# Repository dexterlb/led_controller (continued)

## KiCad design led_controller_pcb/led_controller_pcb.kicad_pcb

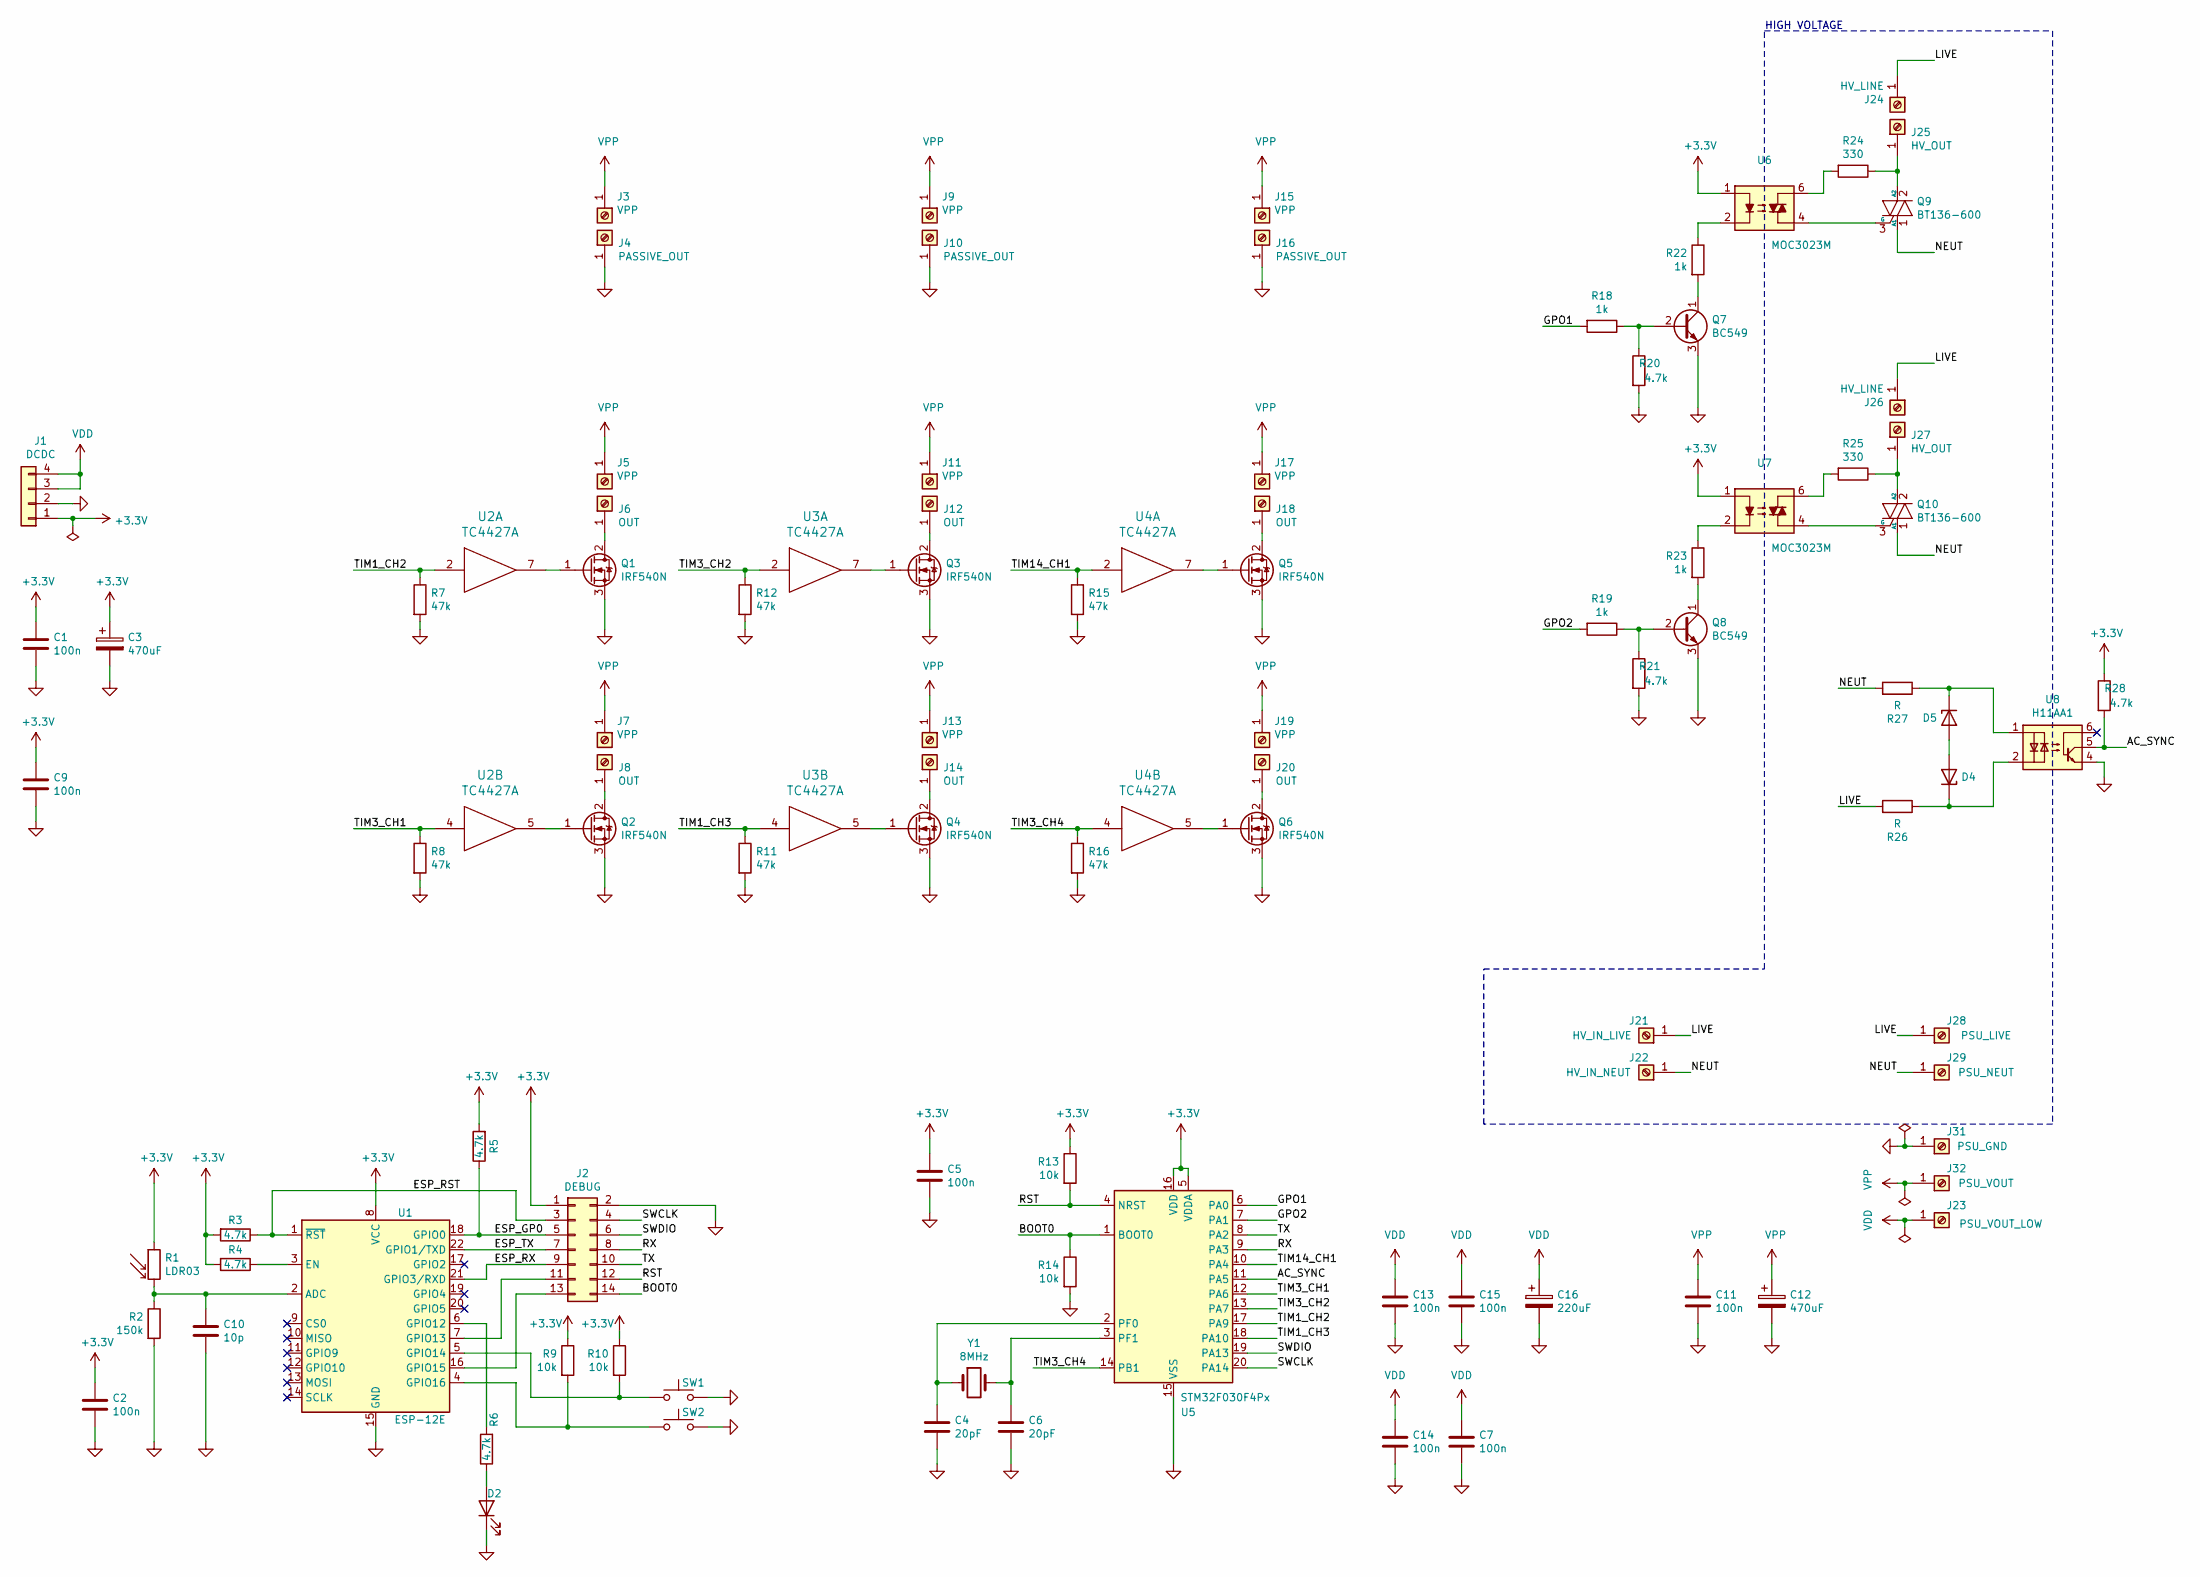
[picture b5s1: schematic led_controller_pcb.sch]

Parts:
C1, C2, C5, C7, C9, C11, C13, C14, C15: 100n; C_0805_2012Metric_Pad1.15x1.40mm_HandSolder
C3: 470uF; CP_Elec_6.3x7.7
C4, C6: 20pF; C_0805_2012Metric_Pad1.15x1.40mm_HandSolder
C10: 10p; C_0805_2012Metric_Pad1.15x1.40mm_HandSolder
C12: 470uF; CP_Radial_D8.0mm_P3.50mm
C16: 220uF; CP_Elec_6.3x7.7
D2: LED; LED_D5.0mm
D4, D5: 1N47xxA; D_DO-41_SOD81_P10.16mm_Horizontal
J1: DCDC; PinHeader_1x04_P2.54mm_Vertical
J2: DEBUG; PinHeader_2x07_P2.54mm_Vertical
J3, J5, J7, J9, J11, J13, J15, J17, J19: VPP; 1PIN_DG306
J4, J10, J16: PASSIVE_OUT; 1PIN_DG306
J6, J8, J12, J14, J18, J20: OUT; 1PIN_DG306
J21: HV_IN_LIVE; 1PIN_DG306
J22: HV_IN_NEUT; 1PIN_DG306
J23: PSU_VOUT_LOW; 1PIN_DG306
J24, J26: HV_LINE; 1PIN_DG306
J25, J27: HV_OUT; 1PIN_DG306
J28: PSU_LIVE; 1PIN_DG306
J29: PSU_NEUT; 1PIN_DG306
J31: PSU_GND; 1PIN_DG306
J32: PSU_VOUT; 1PIN_DG306
Q1, Q2, Q3, Q4, Q5, Q6: IRF540N; TO-220-3_Vertical
Q7, Q8: BC549; TO-92
Q9, Q10: BT136-600; TO-220-3_Vertical
R1: LDR03; PinHeader_1x02_P2.54mm_Vertical
R2: 150k; R_0805_2012Metric_Pad1.15x1.40mm_HandSolder
R3, R4, R5, R6, R20, R21, R28: 4.7k; R_0805_2012Metric_Pad1.15x1.40mm_HandSolder
R7, R8, R11, R12, R15, R16: 47k; R_0805_2012Metric_Pad1.15x1.40mm_HandSolder
R9, R10, R13, R14: 10k; R_0805_2012Metric_Pad1.15x1.40mm_HandSolder
R18, R19, R22, R23: 1k; R_0805_2012Metric_Pad1.15x1.40mm_HandSolder
R24, R25: 330; R_Axial_DIN0207_L6.3mm_D2.5mm_P10.16mm_Horizontal
R26, R27: R; R_Axial_DIN0207_L6.3mm_D2.5mm_P10.16mm_Horizontal
SW1, SW2: BUTTON; PinHeader_1x02_P2.54mm_Vertical
U1: ESP-12E
U2, U3, U4: TC4427A; SOIC-8_3.9x4.9mm_P1.27mm
U5: STM32F030F4Px; TSSOP-20_4.4x6.5mm_P0.65mm
U6, U7: MOC3023M; DIP-6_W7.62mm
U8: H11AA1; DIP-6_W7.62mm
Y1: 8MHz; Crystal_SMD_HC49-SD

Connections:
+3V3: C1.1, C2.1, C3.1, C5.1, C9.1, J1.1, J2.1, R1.1, R3.2, R4.2, R5.2, R9.1, R10.1, R13.1, R28.1, U1.8 (VCC), U5.5 (VDDA), U5.16 (VDD), U6.1, U7.1
/AC_SYNC: R28.2, U5.11 (PA5), U8.5
/BOOT0: J2.14, R14.1, U5.1 (BOOT0)
/ESP_GP0: J2.5, R5.1, U1.18 (GPIO0)
/ESP_RST: J2.3, R3.1, U1.1 (~RST)
/ESP_RX: J2.9, U1.21 (GPIO3/RXD)
/ESP_TX: J2.7, U1.22 (GPIO1/TXD)
/GPO1: R18.2, U5.6 (PA0)
/GPO2: R19.2, U5.7 (PA1)
/LIVE: J21.1, J24.1, J26.1, J28.1, R26.2
/NEUT: J22.1, J29.1, Q9.1 (A1), Q10.1 (A1), R27.2
/RST: J2.12, R13.2, U5.4 (NRST)
/RX: J2.8, U5.9 (PA3)
/SWCLK: J2.4, U5.20 (PA14)
/SWDIO: J2.6, U5.19 (PA13)
/TIM1_CH2: R7.1, U2.2 (IN), U5.17 (PA9)
/TIM1_CH3: R11.1, U3.4 (IN), U5.18 (PA10)
/TIM3_CH1: R8.1, U2.4 (IN), U5.12 (PA6)
/TIM3_CH2: R12.1, U3.2 (IN), U5.13 (PA7)
/TIM3_CH4: R16.1, U4.4 (IN), U5.14 (PB1)
/TIM14_CH1: R15.1, U4.2 (IN), U5.10 (PA4)
/TX: J2.10, U5.8 (PA2)
GND: C1.2, C2.2, C3.2, C4.2, C5.2, C6.2, C7.2, C9.2, C10.2, C11.2, C12.2, C13.2, C14.2, C15.2, C16.2, D2.1 (K), J1.2, J2.2, J4.1, J10.1, J16.1, J31.1, Q1.3 (S), Q2.3 (S), Q3.3 (S), Q4.3 (S), Q5.3 (S), Q6.3 (S), Q7.3 (E), Q8.3 (E), R2.2, R7.2, R8.2, R11.2, R12.2, R14.2, R15.2, R16.2, R20.2, R21.2, SW1.2, SW2.2, U1.15 (GND), U2.3 (GND), U3.3 (GND), U4.3 (GND), U5.15 (VSS), U8.4
unnamed: C4.1, U5.2 (PF0), Y1.1
unnamed: C6.1, U5.3 (PF1), Y1.2
unnamed: C10.1, R1.2, R2.1, U1.2 (ADC)
unnamed: D2.2 (A), R6.1
unnamed: D4.1 (K), R26.1, U8.2
unnamed: D4.2 (A), D5.2 (A)
unnamed: D5.1 (K), R27.1, U8.1
unnamed: J2.11, U1.7 (GPIO13)
unnamed: J2.13, U1.16 (GPIO15)
unnamed: J6.1, Q1.2 (D)
unnamed: J8.1, Q2.2 (D)
unnamed: J12.1, Q3.2 (D)
unnamed: J14.1, Q4.2 (D)
unnamed: J18.1, Q5.2 (D)
unnamed: J20.1, Q6.2 (D)
unnamed: J25.1, Q9.2 (A2), R24.1
unnamed: J27.1, Q10.2 (A2), R25.1
unnamed: Q1.1 (G), U2.7 (Out)
unnamed: Q2.1 (G), U2.5 (Out)
unnamed: Q3.1 (G), U3.7 (Out)
unnamed: Q4.1 (G), U3.5 (Out)
unnamed: Q5.1 (G), U4.7 (Out)
unnamed: Q6.1 (G), U4.5 (Out)
unnamed: Q7.1 (C), R22.2
unnamed: Q7.2 (B), R18.1, R20.1
unnamed: Q8.1 (C), R23.2
unnamed: Q8.2 (B), R19.1, R21.1
unnamed: Q9.3 (G), U6.4
unnamed: Q10.3 (G), U7.4
unnamed: R4.1, U1.3 (EN)
unnamed: R6.2, U1.6 (GPIO12)
unnamed: R9.2, SW2.1, U1.4 (GPIO16)
unnamed: R10.2, SW1.1, U1.5 (GPIO14)
unnamed: R22.1, U6.2
unnamed: R23.1, U7.2
unnamed: R24.2, U6.6
unnamed: R25.2, U7.6
VDD: C7.1, C13.1, C14.1, C15.1, C16.1, J1.3, J1.4, J23.1, U2.6 (VDD), U3.6 (VDD), U4.6 (VDD)
VPP: C11.1, C12.1, J3.1, J5.1, J7.1, J9.1, J11.1, J13.1, J15.1, J17.1, J19.1, J32.1

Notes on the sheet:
HIGH VOLTAGE

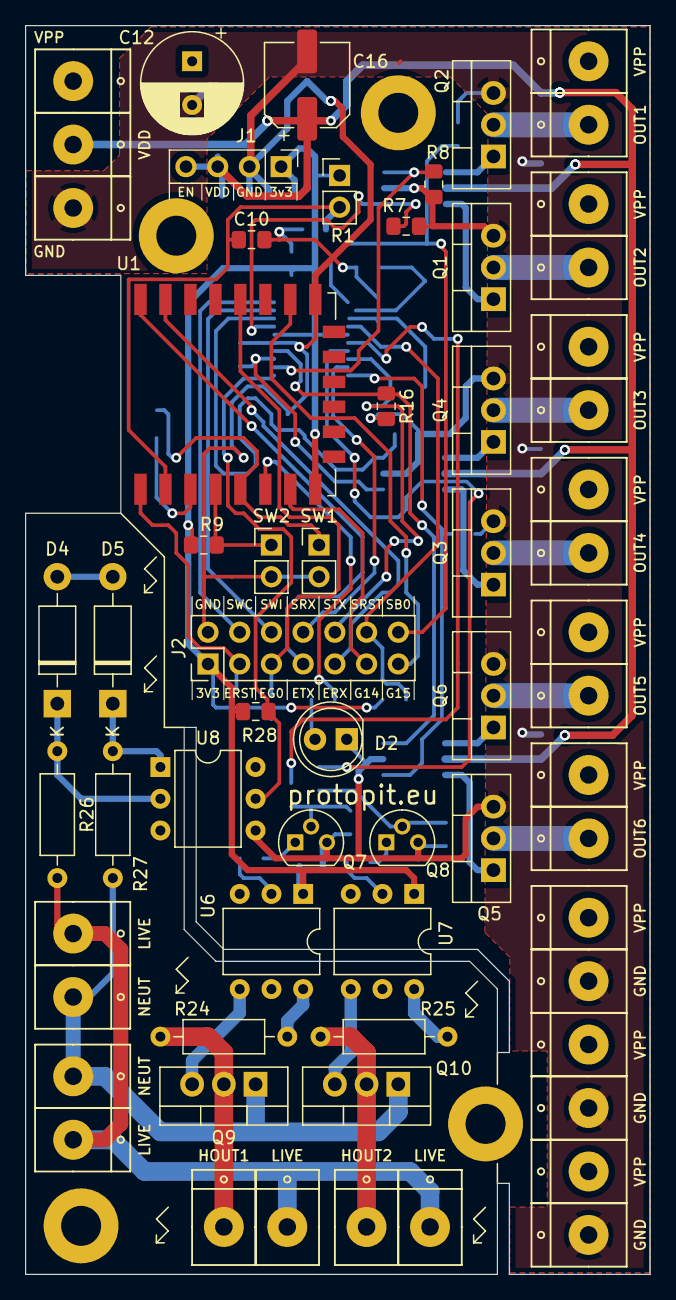
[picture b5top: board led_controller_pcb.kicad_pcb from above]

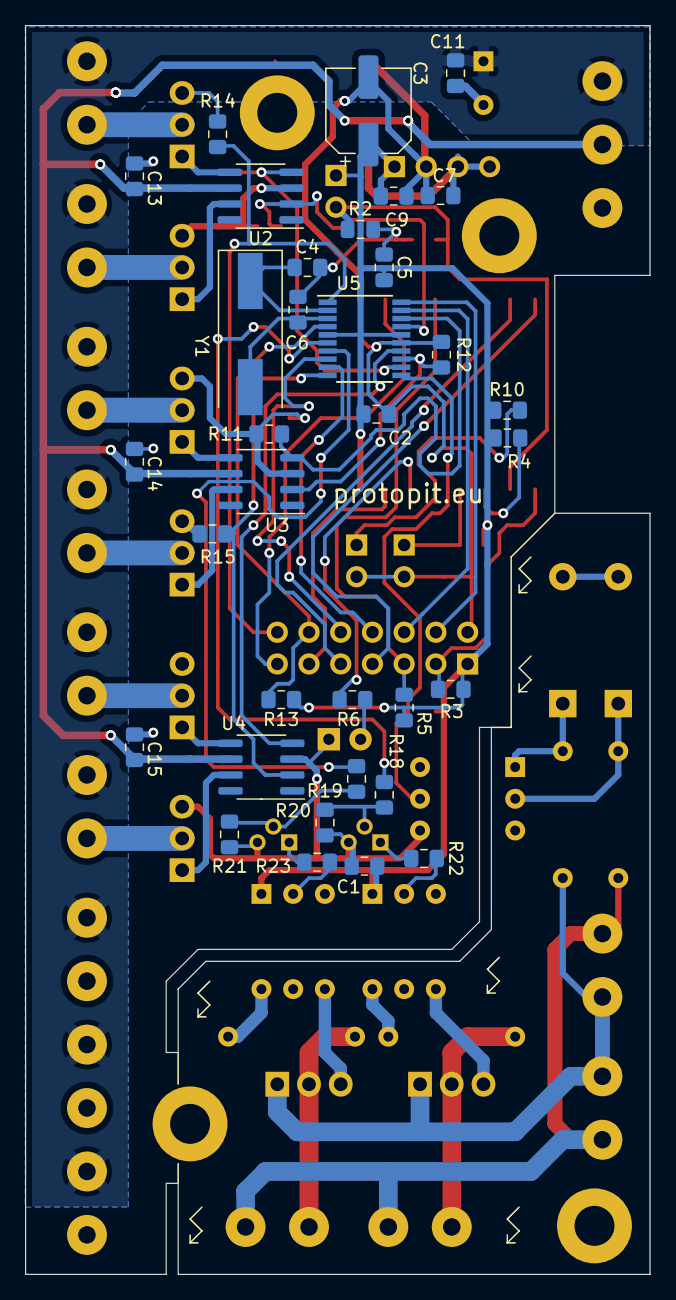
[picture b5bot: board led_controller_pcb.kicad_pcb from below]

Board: 2 copper layers, 50.0 x 100.0 mm, 97 parts (34 on the bottom side), 62 nets.

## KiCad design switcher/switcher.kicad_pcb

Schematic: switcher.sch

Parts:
C1, C2, C7: 100n; C_0805_2012Metric_Pad1.15x1.40mm_HandSolder
C3, C8: 470uF; CP_Radial_D8.0mm_P3.50mm
C10: 10p; C_0805_2012Metric_Pad1.15x1.40mm_HandSolder
D2: LED; LED_D5.0mm
J1: DCDC; PinHeader_1x04_P2.54mm_Vertical
J2: USB_B_Micro; USB_Micro-B_ATTEND
J3: Power; PinHeader_1x02_P2.54mm_Vertical
J4, J16: POWER_OUT; PinHeader_1x03_P2.54mm_Vertical
J5, J8, J9, J10: O1; PinHeader_1x04_P2.54mm_Vertical
J6: O2; PinHeader_1x04_P2.54mm_Vertical
J7: O3; PinHeader_1x04_P2.54mm_Vertical
J11: I1; PinHeader_1x04_P2.54mm_Vertical
J12: I2; PinHeader_1x04_P2.54mm_Vertical
J13: I3; PinHeader_1x04_P2.54mm_Vertical
J14: Barrel_Jack_Switch; BarrelJack_Horizontal
J17: DEBUG; PinHeader_1x06_P2.54mm_Vertical
JP1, JP2, JP3: VSEL; PinHeader_2x02_P2.54mm_Vertical
Q1, Q2, Q3, Q4, Q5, Q6: BC817; SOT-23
R1: LDR03; PinHeader_1x02_P2.54mm_Vertical
R2: 150k; R_0805_2012Metric_Pad1.15x1.40mm_HandSolder
R3, R4, R5, R6, R8, R10, R13, R14, R17, R21, R22, R24, R27: 4.7k; R_0805_2012Metric_Pad1.15x1.40mm_HandSolder
R7, R9, R11, R12, R15, R16, R18, R19, R20, R23, R25, R26: 1k; R_0805_2012Metric_Pad1.15x1.40mm_HandSolder
U1: ESP-12E

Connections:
+3V3: C1.1, C2.1, C3.1, J1.1, J4.2, J5.3, J6.3, J7.3, J8.3, J9.3, J10.3, J11.3, J12.3, J13.3, J16.2, J17.1, R1.1, R3.2, R4.2, R5.2, R9.1, R15.1, R16.1, R23.1, R25.1, R26.1, U1.8 (VCC)
/ESP_GP0: J17.2, R5.1, U1.18 (GPIO0)
/ESP_RST: J17.3, R3.1, U1.1 (~RST)
/ESP_RX: J17.5, U1.21 (GPIO3/RXD)
/ESP_TX: J17.4, U1.22 (GPIO1/TXD)
/GP1: J8.1, U1.16 (GPIO15)
/GP2: J9.1, U1.4 (GPIO16)
/GP3: J10.1, U1.11 (GPIO9)
/GPI1: Q2.3 (C), R9.2, U1.7 (GPIO13)
/GPI2: Q4.3 (C), R16.2, U1.6 (GPIO12)
/GPI3: Q6.3 (C), R26.2, U1.5 (GPIO14)
/GPO1: R19.2, U1.17 (GPIO2)
/GPO2: R11.2, U1.19 (GPIO4)
/GPO3: R18.2, U1.20 (GPIO5)
/I1: J11.1, R7.2
/I2: J12.1, R12.2
/I3: J13.1, R20.2
/O1: J5.1, JP1.1, JP1.3, Q1.3 (C)
/O2: J6.1, JP2.1, JP2.3, Q3.3 (C)
/O3: J7.1, JP3.1, JP3.3, Q5.3 (C)
GND: C1.2, C2.2, C3.2, C7.2, C8.2, C10.2, D2.1 (K), J1.2, J2.5 (GND), J2.6 (Shield), J3.1, J4.1, J5.2, J6.2, J7.2, J8.2, J9.2, J10.2, J11.2, J12.2, J13.2, J14.2, J16.1, J17.6, Q1.2 (E), Q2.2 (E), Q3.2 (E), Q4.2 (E), Q5.2 (E), Q6.2 (E), R2.2, R8.2, R13.2, R14.2, R21.2, R22.2, R24.2, U1.15 (GND)
unnamed: C10.1, R1.2, R2.1, U1.2 (ADC)
unnamed: D2.2 (A), R6.1
unnamed: JP1.2, R23.2
unnamed: JP1.4, R10.2
unnamed: JP2.2, R15.2
unnamed: JP2.4, R17.2
unnamed: JP3.2, R25.2
unnamed: JP3.4, R27.2
unnamed: Q1.1 (B), R19.1, R21.1
unnamed: Q2.1 (B), R7.1, R8.1
unnamed: Q3.1 (B), R11.1, R13.1
unnamed: Q4.1 (B), R12.1, R14.1
unnamed: Q5.1 (B), R18.1, R22.1
unnamed: Q6.1 (B), R20.1, R24.1
unnamed: R4.1, U1.3 (EN)
unnamed: R6.2, U1.12 (GPIO10)
VDD: C7.1, C8.1, J1.3, J1.4, J2.1 (VBUS), J3.2, J4.3, J5.4, J6.4, J7.4, J8.4, J9.4, J10.4, J11.4, J12.4, J13.4, J14.1, J16.3, R10.1, R17.1, R27.1

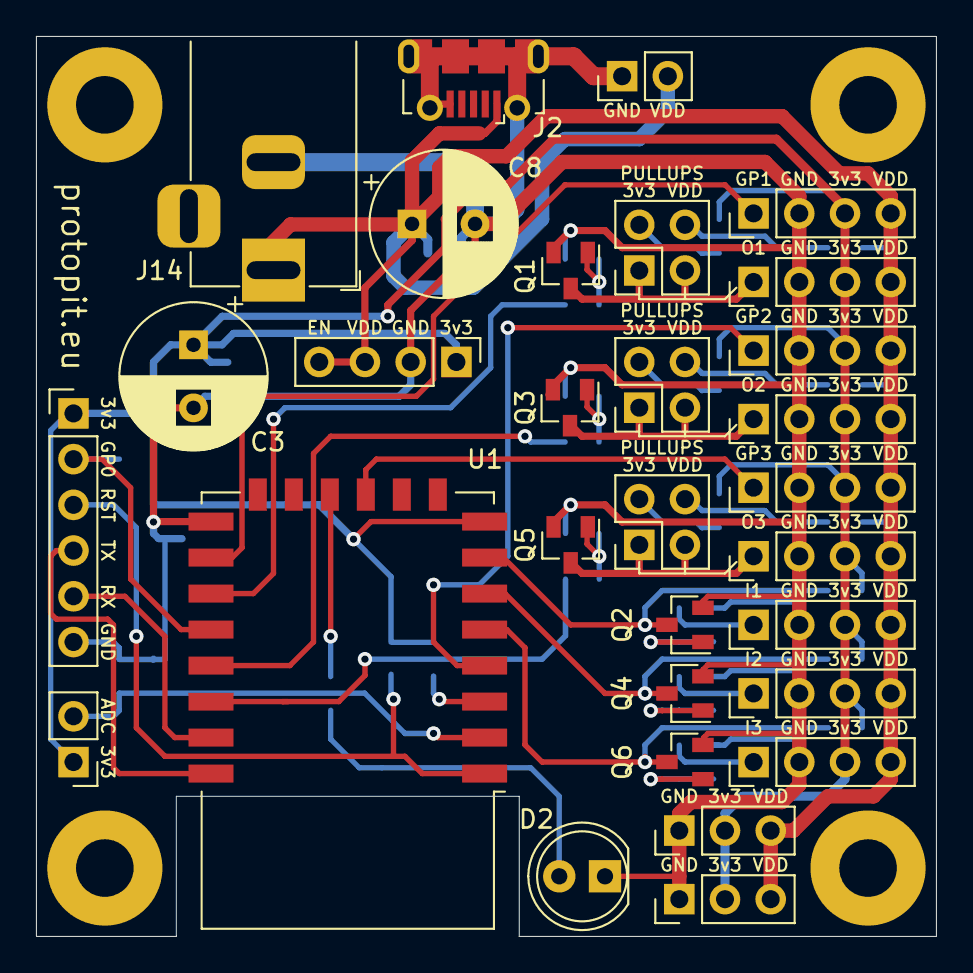
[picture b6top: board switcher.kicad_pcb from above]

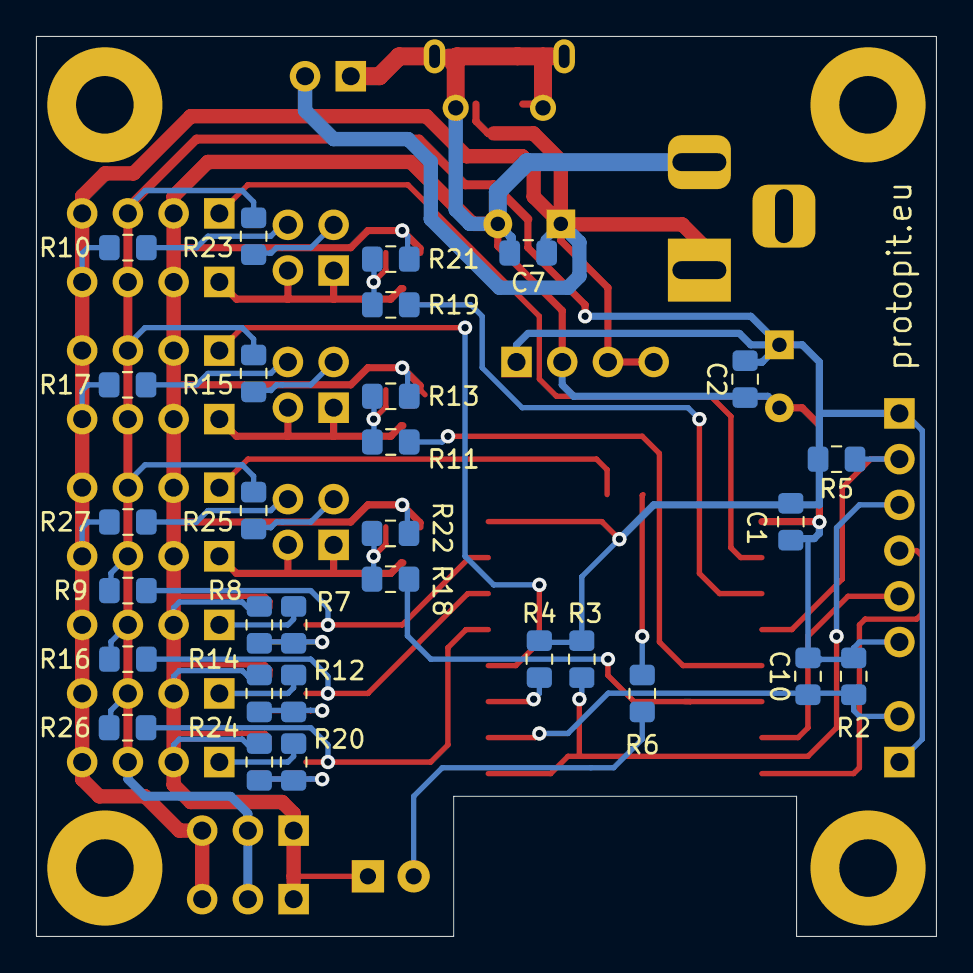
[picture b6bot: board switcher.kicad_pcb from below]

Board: 2 copper layers, 50.0 x 50.0 mm, 60 parts (30 on the bottom side), 38 nets.

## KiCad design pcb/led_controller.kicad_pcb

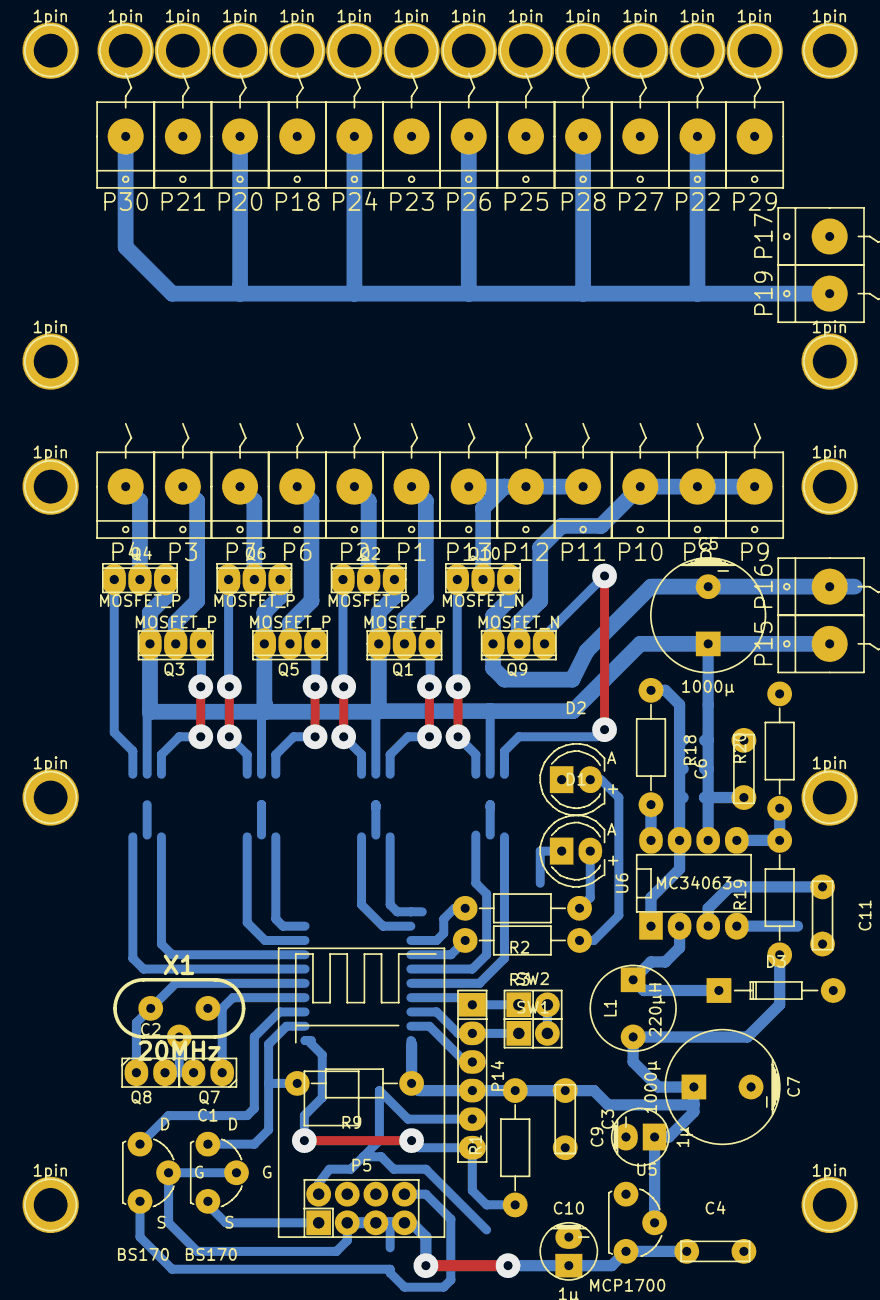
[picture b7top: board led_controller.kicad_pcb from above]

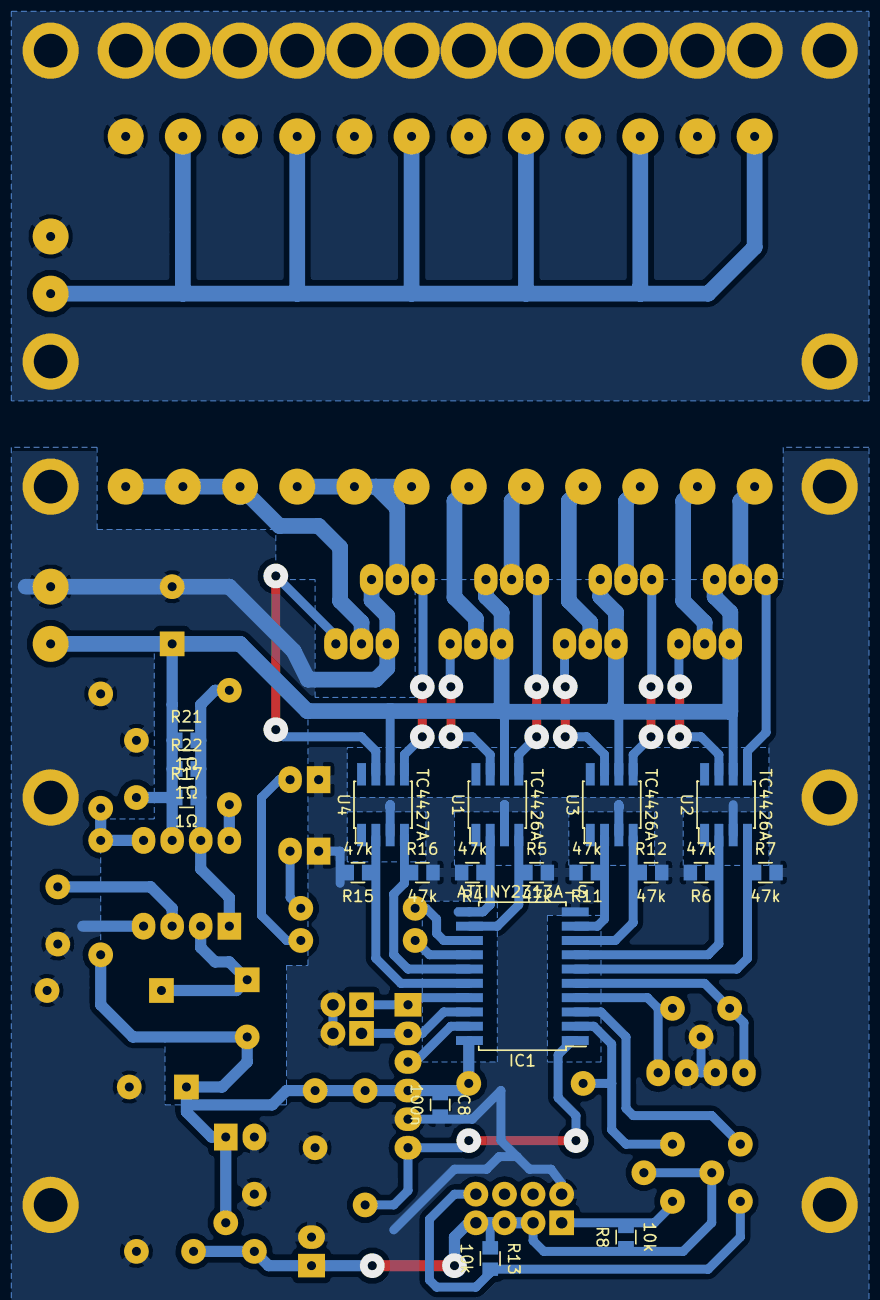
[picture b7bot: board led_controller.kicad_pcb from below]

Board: 2 copper layers, 107 parts (19 on the bottom side), 49 nets.

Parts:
1pin, 1pin#2, 1pin#3, 1pin#4, 1pin#5, 1pin#6, 1pin#7, 1pin#8, 1pin#9, 1pin#10, 1pin#11, 1pin#12, 1pin#13, 1pin#14, 1pin#15, 1pin#16, 1pin#17, 1pin#18, 1pin#19, 1pin#20, 1pin#21, 1pin#22: VAL**; 1pin
C1, C2: 22p; Capacitor3MMDiscRM2.5
C3, C4, C6: 100n; Capacitor6MMDiscRM5
C5, C7: 1000μ; Capacitor10x16RM5
C8: 100n; C_0805
C9, C10: 1μ; Capacitor5x6RM2.5
C11: 470p; Capacitor6MMDiscRM5
D1, D2: LED; Diode_LED_5mm_round_vertical
D3: BYV10-40; Diode_DO-35_SOD27_Horizontal_RM10
IC1: ATTINY2313A-S; SOIC-20_7.5x12.8mm_Pitch1.27mm
L1: 220μH; INDUCTOR_V
P1: POSITIVE_OUT_1; 1PIN_DG306
P2: POSITIVE_OUT_2; 1PIN_DG306
P3: POSITIVE_OUT_3; 1PIN_DG306
P4: POSITIVE_OUT_4; 1PIN_DG306
P5: ESP8266; ESP8266_Module
P6: POSITIVE_OUT_5; 1PIN_DG306
P7: POSITIVE_OUT_6; 1PIN_DG306
P8, P9, P10: NEGATIVE_OUT_1; 1PIN_DG306
P11, P12, P13: NEGATIVE_OUT_2; 1PIN_DG306
P14: ISP; Pin_Header_Straight_1x06
P15: +12v_IN; 1PIN_DG306
P16, P17: GND_IN; 1PIN_DG306
P18, P21, P23, P25, P27, P29: GND_OUT; 1PIN_DG306
P19: VDD_IN; 1PIN_DG306
P20, P22, P24, P26, P28, P30: VDD_OUT; 1PIN_DG306
Q1, Q2, Q3, Q4, Q5, Q6: MOSFET_P; IPAK-3_GDS
Q7, Q8: BS170; TO-92-FET-molded-wide-DGS
Q9, Q10: MOSFET_N; IPAK-3_GDS
R1, R9: 10k; Resistor_Horizontal_RM10mm
R2, R3: 1k; Resistor_Horizontal_RM10mm
R4, R5, R6, R7, R11, R12, R15, R16: 47k; R_0805
R8, R13: 10k; R_0805
R17, R21, R22: 1Ω; R_0805
R18: 180Ω; Resistor_Horizontal_RM10mm
R19: 3.6k; Resistor_Horizontal_RM10mm
R20: 1.2k; Resistor_Horizontal_RM10mm
SW1: B1; Pin_Header_Straight_1x02
SW2: B2; Pin_Header_Straight_1x02
U1, U2, U3: TC4426A; SOIC-8_3.9x4.9mm_Pitch1.27mm
U4: TC4427A; SOIC-8_3.9x4.9mm_Pitch1.27mm
U5: MCP1700; TO-92-Free-molded-wide
U6: MC34063; DIP-8__300
X1: 20MHz; HC-49V

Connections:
+3V3: C4.1, C10.1, P5.3, P5.5, P5.7, Q7.G, Q8.G, R8.1, R13.1, U5.3
+5V: C3.1, C7.1, C8.1, C9.1, IC1.20, L1.2, P14.4, R1.2, R9.1, R19.1, U5.2
/MISO: IC1.18, P14.2, SW1.1
/MOSI: IC1.17, P14.1, SW2.1
/N1: IC1.16, R15.1, U4.2
/N2: IC1.15, R16.1, U4.4
/P1: IC1.11, R4.1, U1.2
/P2: IC1.12, R5.1, U1.4
/P3: IC1.7, R6.1, U2.2
/P4: IC1.6, R7.1, U2.4
/P5: IC1.9, R11.1, U3.2
/P6: IC1.8, R12.1, U3.4
/Power Supply/GND2: 1pin.1, 1pin#3.1, 1pin#5.1, 1pin#6.1, 1pin#7.1, 1pin#8.1, 1pin#9.1, 1pin#10.1, 1pin#11.1, 1pin#12.1, 1pin#13.1, 1pin#14.1, 1pin#15.1, 1pin#16.1, 1pin#17.1, 1pin#18.1, P17.1, P18.1, P21.1, P23.1, P25.1, P27.1, P29.1
/RESET: IC1.1, P14.6, R1.1
/RX_AVR: IC1.2, Q7.D, R9.2
/RX_WIFI: P5.8, Q8.S, R13.2
/SCK: IC1.19, P14.3
/TX_AVR: IC1.3, Q8.D
/TX_WIFI: P5.1, Q7.S, R8.2
GND: 1pin#2.1, 1pin#4.1, 1pin#19.1, 1pin#20.1, 1pin#21.1, 1pin#22.1, C1.2, C2.2, C3.2, C4.2, C5.2, C6.2, C7.2, C8.2, C9.2, C10.2, C11.2, D1.2, D2.2, D3.1, IC1.10, P5.2, P14.5, P16.1, Q9.S, Q10.S, R4.2, R5.2, R6.2, R7.2, R11.2, R12.2, R15.2, R16.2, R20.2, SW1.2, SW2.2, U1.3, U2.3, U3.3, U4.3, U5.1, U6.4, X1.0
unnamed: C1.1, IC1.4, X1.2
unnamed: C2.1, IC1.5, X1.1
unnamed: C11.1, U6.3
unnamed: D1.1, R2.1
unnamed: D2.1, R3.1
unnamed: D3.2, L1.1, U6.2
unnamed: IC1.13, R2.2
unnamed: IC1.14, R3.2
unnamed: P1.1, Q1.D
unnamed: P2.1, Q2.D
unnamed: P3.1, Q3.D
unnamed: P4.1, Q4.D
unnamed: P6.1, Q5.D
unnamed: P7.1, Q6.D
unnamed: P8.1, P9.1, P10.1, Q9.D
unnamed: P11.1, P12.1, P13.1, Q10.D
unnamed: P19.1, P20.1, P22.1, P24.1, P26.1, P28.1, P30.1
unnamed: Q1.G, U1.7
unnamed: Q2.G, U1.5
unnamed: Q3.G, U2.7
unnamed: Q4.G, U2.5
unnamed: Q5.G, U3.7
unnamed: Q6.G, U3.5
unnamed: Q9.G, U4.7
unnamed: Q10.G, U4.5
unnamed: R17.2, R18.1, R21.2, R22.2, U6.1, U6.7
unnamed: R18.2, U6.8
unnamed: R19.2, R20.1, U6.5
VDD: C5.1, C6.1, P15.1, Q1.S, Q2.S, Q3.S, Q4.S, Q5.S, Q6.S, R17.1, R21.1, R22.1, U1.6, U2.6, U3.6, U4.6, U6.6

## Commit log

2016-09-26 initial
2016-09-26 draw general idea of schematic
2016-09-27 assign footprints
2016-09-27 synchronise components to PCB
2016-09-27 5v step-down
2016-09-28 arrange mosfets
2016-09-28 draw symbol and footprint for the esp8266 module
2016-09-29 connect drivers to the mcu
2016-09-29 everything except power supply
2016-09-29 position power supply
2016-09-29 arrange everything
2016-09-29 add power planes
2016-09-30 remove title block from schematic
2016-10-01 some 3D models
2016-10-01 second PCB
2018-02-17 lua files for nodemcu
2018-02-17 read keapalive time from credentials
2018-02-17 nicer subscriptions
2018-02-18 parse UART
2018-02-22 fix bugs with communication
2018-02-22 add credentials
2018-02-22 kicad version update
2018-02-22 add some AVR code
2018-02-22 vscode settings
2018-02-22 pwm works
2018-02-22 floats
2018-02-22 use integer brightness
2018-02-22 more parsing
2018-02-22 proper brightness low and high limits
2018-02-23 start with zero brightness
2018-02-23 lua support for integer brightness
2018-02-23 update hardware definitions
2018-02-23 some lua fixes
2018-02-28 some last-minute fixes
2019-09-17 cleanup
2019-09-17 new version of pcb
2019-09-18 label mcu pins
2019-09-20 some more schematic work
2019-09-20 finalise schematic
2019-09-30 pcb taking shape
2019-09-30 pcb all connected
2019-09-30 finish pcb
2019-10-02 adjust for old kicad version
2019-10-02 ditch the avr project
2019-10-02 add stm32 code
2019-10-02 the battle against TIM1 goes strong
2019-10-04 fix tim1 pwm
2019-10-04 recalculate pwm frequency
2019-10-05 reroute traces to use other timer
2019-10-09 finalise PCB
2019-10-09 add resistor
2019-10-09 correct size of pcb
2019-10-09 update schematic
2019-11-28 new architecture
2019-12-01 generate full contract
2019-12-22 potoo contract
2020-03-08 wip on adding a separate connector for high voltage
2020-03-09 cosmetic fixes
2020-03-09 some more cosmetic changes
2020-03-09 update gitignore to ignore some more kicad files
2020-03-09 add switcher board
2020-03-31 cosmetic changes to led controller pcb
2020-03-31 finish the switcher pcb
2020-04-04 add stepper project
2020-04-04 driver_motor library and some changes to switcher
2020-04-11 jumpers library
2020-04-11 stepper pcb
2020-04-11 minor changes
2020-04-11 update 0805 components to have larger pads
2020-04-11 cosmetic changes
2020-04-11 add library caches
    the kicad projects may now be opened without installed libraries
2020-04-11 encoder project
2020-11-30 test uart
2020-11-30 update kicad files
2020-11-30 update gitignore and some missing kicad files
2020-11-30 add led board
2020-11-30 add nodemcu stuff
2020-11-30 add nodemcu old app
2020-12-02 update pcb
2020-12-02 uart message processing
2020-12-02 migrate from *.pro to *.kicad_pro
2020-12-02 ignore kicad backups dirs
2020-12-02 properly handle messages
2020-12-02 move all uart code to uart.c
2020-12-02 double-buffer uart receives
2020-12-02 supply uart receive handler by function pointer; comments and checks
2020-12-03 add some uart todos
2020-12-03 argument splitting
2020-12-04 semi-appropriate input parsing
2020-12-04 state getters
2020-12-08 boilerplate for periodic state updates
2020-12-08 fading and gamma
2020-12-09 pwm updates
2020-12-09 fix stupid bug in split_string
2020-12-09 use fixed point instead of floating point to save space
2020-12-09 less stupid scale_int
2020-12-10 separate gamma; optional debug
2020-12-11 rework pwm control to eliminate jumps when adjusting value
2020-12-11 allow reversing polarity and alignment of pwm
2020-12-11 remove paired channel functionality
2020-12-11 add set.sh
2020-12-11 support multiple commands per line
2020-12-11 fix stupid pcb mistake
2020-12-13 properly space leds on pcb
2020-12-15 rearrange led board pcb
2020-12-15 properly blend lamp colours
2020-12-15 animate blend
2020-12-15 allow parsing fixedpt numbers with no decimal point
2020-12-22 organise board files
2020-12-22 add analog pwm experiment
2021-02-01 add dimmable psu project
2021-02-01 add pwm bus module
2021-02-01 add buck converter ic
2021-02-01 update led board kicad versions
2021-02-02 add frugal a4 schematic template
2021-02-02 current adjustment reference voltage generator
2021-02-03 analog logic for dimming and clamping
2021-02-03 update some kicad versions
2021-02-04 add some calculations in a text file
2021-02-04 A3 schematic template
2021-02-04 more or less a final version of the dimmable psu schematic
2021-02-05 footprint for inductor
2021-02-05 some more touches to dimmable_psu schematic
2021-02-05 update psu calculations
2021-02-08 add some wago footprints
2021-02-08 final touches to dimmable psu schematic
2021-02-08 proper footprint for opamp
2021-02-10 mounting holes!
2021-02-13 arrange power-side stuff
2021-02-13 some more pcb work
2021-02-16 use dip switches instead of jumpers
2021-03-04 analog_pwm -> complementary_pwm
2021-03-04 some more work on dimmable psu pcb
2021-03-08 rework dimmable_psu opamp power supplies
2021-03-08 random cosmetic stuff
2021-03-15 dimmable psu pcb almost finished
2021-03-15 add pwm controller
2021-03-16 add filled areas and make some cosmetic fixes
2021-03-30 replace LDOs with npns
2021-04-11 reorganise pcb
2021-05-02 restore zones
2021-05-02 rearrange
2021-05-03 use 1206 power resistors
2021-05-03 arrangement works
2021-05-03 overvoltage limit resistor
2021-11-03 update kicad
2022-01-24 reorganise dirs
2022-01-24 rename
2024-01-02 add fast pwm controller schematic
2024-01-02 add sim files
2024-01-02 this commit is vomit
2024-01-02 add external kicad libs
2024-01-03 buck converter can now be switched off via jumper
2024-01-03 basic external layout of board
2024-01-13 almost finish arranging the fast pwm controller pcb
2024-01-13 prepare traces
2024-01-13 finalise connections
2024-01-15 finalise board
2024-01-16 change connectors
2024-03-01 final touches to the fast pwm controller
